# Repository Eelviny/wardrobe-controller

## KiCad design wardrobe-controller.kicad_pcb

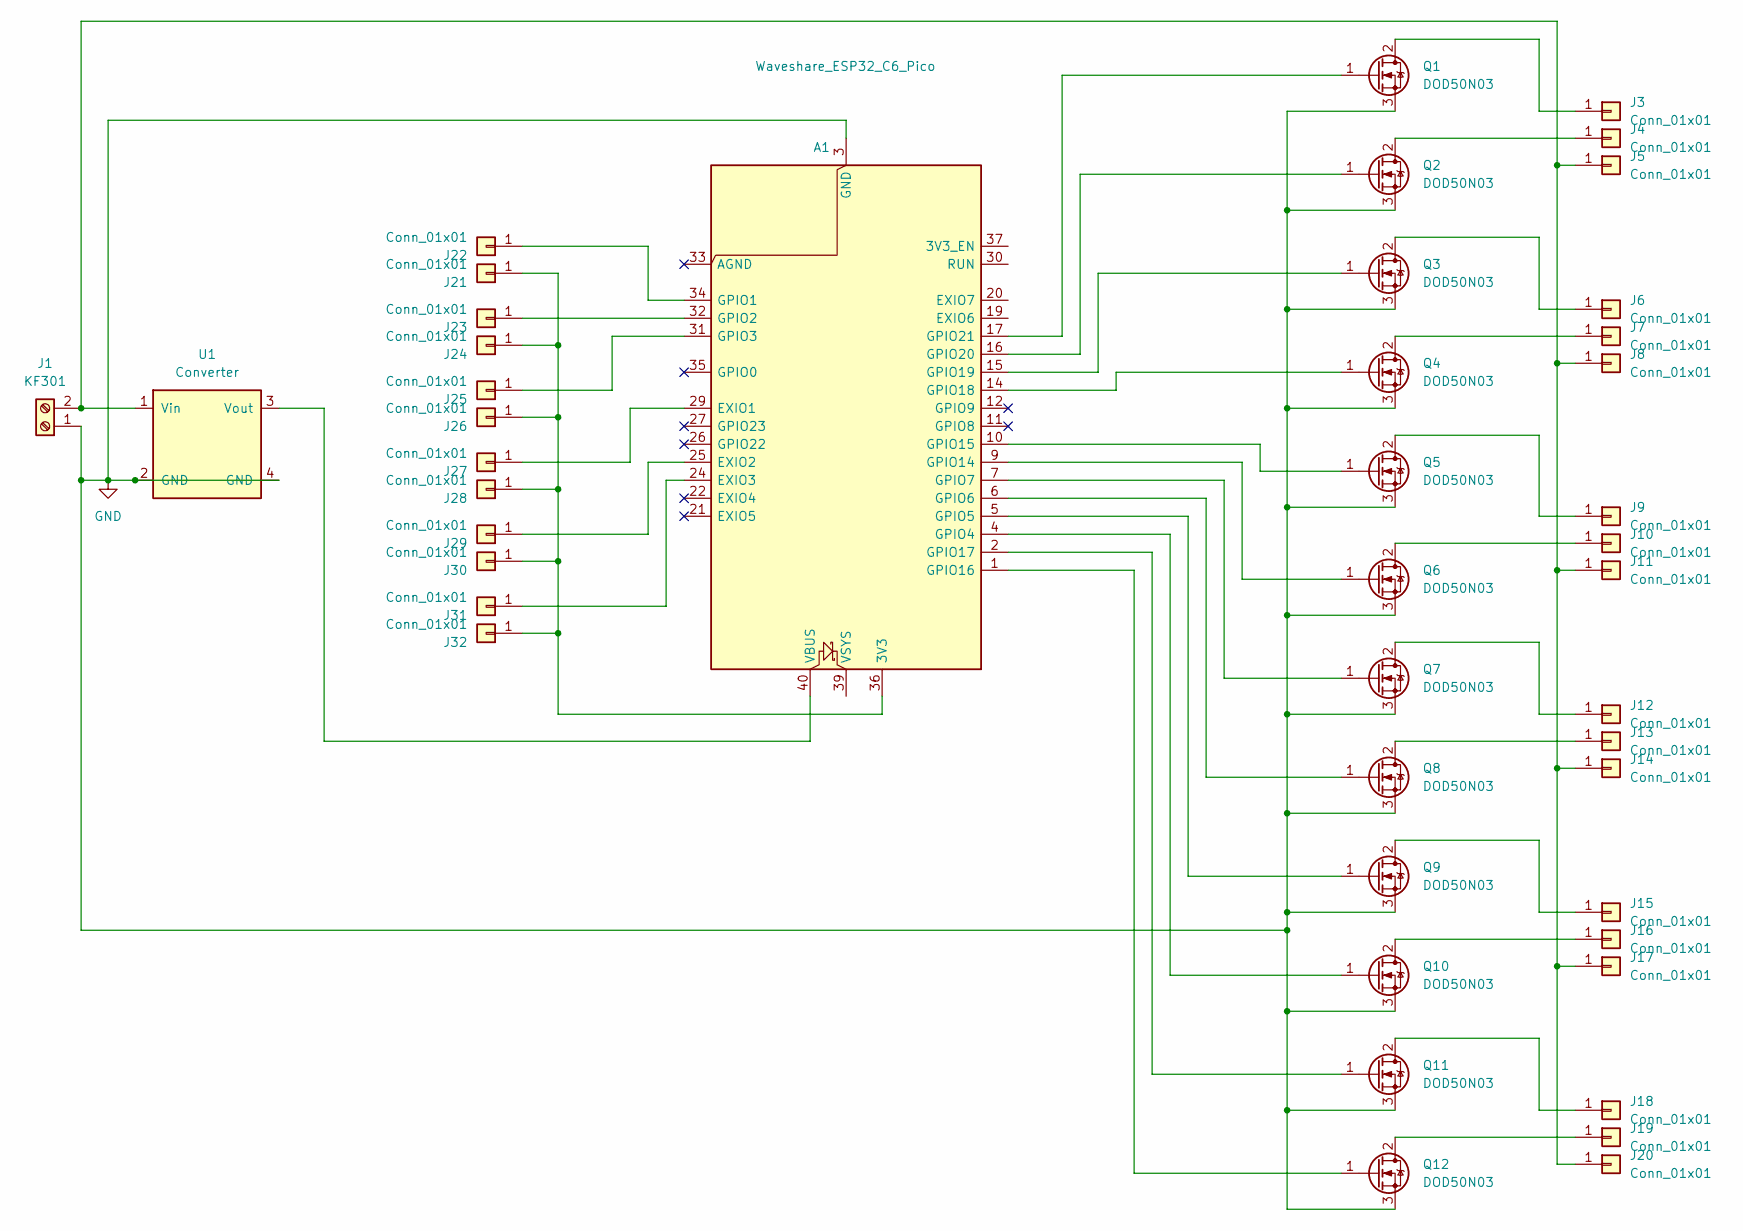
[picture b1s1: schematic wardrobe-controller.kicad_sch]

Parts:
A1: Waveshare_ESP32_C6_Pico; RaspberryPi_Pico_Common
J1: KF301; TerminalBlock_RND_205-00012_1x02_P5.00mm_Horizontal; JLCPCB_IGNORE yes
J3, J4, J5, J6, J7, J8, J9, J10, J11, J12, J13, J14, J15, J16, J17, J18, J19, J20, J21, J22, J23, J24, J25, J26, J27, J28, J29, J30, J31, J32: Conn_01x01; SolderPad; JLCPCB_IGNORE yes
Q1, Q2, Q3, Q4, Q5, Q6, Q7, Q8, Q9, Q10, Q11, Q12: DOD50N03; TO-252-2; LCSC C36499176
U1: Converter; Buck_Converter_Module

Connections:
GND: A1.3 (GND), A1.8 (GND), A1.13 (GND), A1.18 (GND), A1.23 (GND), A1.28 (GND), A1.38 (GND), J1.1, Q1.3 (S), Q2.3 (S), Q3.3 (S), Q4.3 (S), Q5.3 (S), Q6.3 (S), Q7.3 (S), Q8.3 (S), Q9.3 (S), Q10.3 (S), Q11.3 (S), Q12.3 (S), U1.2 (GND), U1.4 (GND)
unnamed: A1.36 (3V3), J21.1, J24.1, J26.1, J28.1, J30.1, J32.1
unnamed: A1.29 (EXIO1), J27.1
unnamed: A1.25 (EXIO2), J29.1
unnamed: A1.24 (EXIO3), J31.1
unnamed: A1.34 (GPIO1), J22.1
unnamed: A1.32 (GPIO2), J23.1
unnamed: A1.31 (GPIO3), J25.1
unnamed: A1.4 (GPIO4), Q10.1 (G)
unnamed: A1.5 (GPIO5), Q9.1 (G)
unnamed: A1.6 (GPIO6), Q8.1 (G)
unnamed: A1.7 (GPIO7), Q7.1 (G)
unnamed: A1.9 (GPIO14), Q6.1 (G)
unnamed: A1.10 (GPIO15), Q5.1 (G)
unnamed: A1.1 (GPIO16), Q12.1 (G)
unnamed: A1.2 (GPIO17), Q11.1 (G)
unnamed: A1.14 (GPIO18), Q4.1 (G)
unnamed: A1.15 (GPIO19), Q3.1 (G)
unnamed: A1.16 (GPIO20), Q2.1 (G)
unnamed: A1.17 (GPIO21), Q1.1 (G)
unnamed: A1.40 (VBUS), U1.3 (Vout)
unnamed: J1.2, J5.1, J8.1, J11.1, J14.1, J17.1, J20.1, U1.1 (Vin)
unnamed: J3.1, Q1.2 (D)
unnamed: J4.1, Q2.2 (D)
unnamed: J6.1, Q3.2 (D)
unnamed: J7.1, Q4.2 (D)
unnamed: J9.1, Q5.2 (D)
unnamed: J10.1, Q6.2 (D)
unnamed: J12.1, Q7.2 (D)
unnamed: J13.1, Q8.2 (D)
unnamed: J15.1, Q9.2 (D)
unnamed: J16.1, Q10.2 (D)
unnamed: J18.1, Q11.2 (D)
unnamed: J19.1, Q12.2 (D)

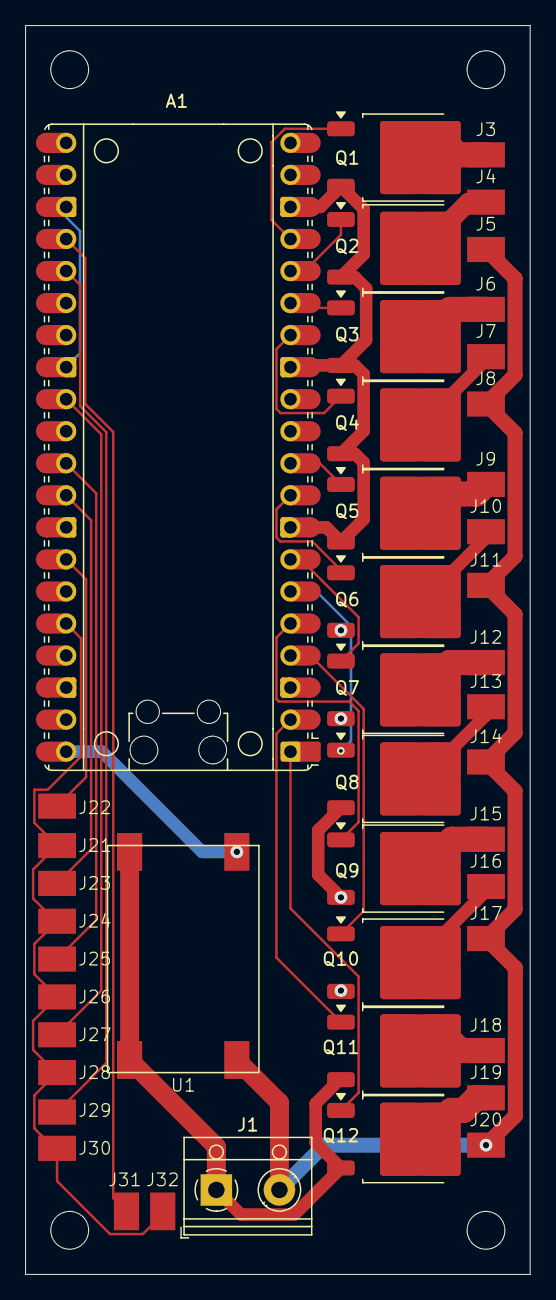
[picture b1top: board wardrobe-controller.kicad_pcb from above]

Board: 2 copper layers, 40.0 x 99.0 mm, 45 parts (0 on the bottom side), 34 nets.

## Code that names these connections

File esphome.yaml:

esphome:
  name: wardrobe
  friendly_name: Wardrobe
  platformio_options:
    board_build.flash_mode: dio
    build_flags: "-DI2C_NUM_1=I2C_NUM_0"
  on_boot:
    then:
      - light.control:
          id: light_1
          state: off
          brightness: 80%
      - light.control:
          id: light_2
          state: off
          brightness: 80%
      - light.control:
          id: light_3
          state: off
          brightness: 80%
      - light.control:
          id: light_4
          state: off
          brightness: 80%

esp32:
  board: esp32-c6-devkitc-1
  variant: ESP32C6
  flash_size: 4MB
  framework:
    type: esp-idf
i2c:
  scan: false
  sda: GPIO22
  scl: GPIO23
  frequency: 400kHz

pca9554:
  - id: "pca9554a_device"

# Enable logging
# logger:
#   hardware_uart: USB_SERIAL_JTAG

api:
  reboot_timeout: 8h
  encryption:
    key: !secret encryption_key

ota:
  - platform: esphome

wifi:
  ssid: !secret wifi_ssid
  password: !secret wifi_password

# esp32_improv:
#   authorizer: none
#   identify_duration: 30s

network:
  enable_ipv6: true

sensor:
  - platform: uptime
    name: Uptime
    id: uptime_sensor
  - platform: wifi_signal
    name: Signal Strength
    id: wifi_sensor

button:
  - platform: restart
    name: Restart
  - platform: safe_mode
    name: Restart (Safe Mode)

switch:
  - platform: template
    id: door_activation
    name: Door Open Activation
    optimistic: true
    icon: mdi:lightbulb-auto
    restore_mode: RESTORE_DEFAULT_ON

output:
  - platform: ledc
    id: warm_white_output_3
    frequency: 9765Hz
    pin:
      number: GPIO15
  # - platform: ledc
  #   id: cold_white_output_3
  #   frequency: 9765Hz
  #   pin:
  #     number: GPIO14
  - platform: gpio
    id: cold_white_output_3
    pin:
      number: GPIO14
  - platform: ledc
    id: warm_white_output_4
    frequency: 9765Hz
    phase_angle: 90
    pin:
      number: GPIO7
  - platform: gpio
    id: cold_white_output_4
    pin:
      number: GPIO6
  # - platform: ledc
  #   id: cold_white_output_4
  #   frequency: 9765Hz
  #   pin:
  #     number: GPIO6
  - platform: ledc
    id: warm_white_output_5
    frequency: 9765Hz
    phase_angle: 180
    pin:
      number: GPIO5
  - platform: gpio
    id: cold_white_output_5
    pin:
      number: GPIO4
  # - platform: ledc
  #   id: cold_white_output_5
  #   frequency: 9765Hz
  #   pin:
  #     number: GPIO4
  - platform: ledc
    id: warm_white_output_6
    frequency: 9765Hz
    phase_angle: 270
    pin:
      number: GPIO17
  - platform: gpio
    id: cold_white_output_6
    pin:
      number: GPIO16
  # - platform: ledc
  #   id: cold_white_output_6
  #   frequency: 9765Hz
  #   pin:
  #     number: GPIO16

light:
  # - platform: esp32_rmt_led_strip
  #   rgb_order: RGB
  #   pin: GPIO8
  #   num_leds: 1
  #   chipset: ws2812
  #   name: "Status LED"
  #   default_transition_length: 0s
  #   disabled_by_default: true
  # - platform: cwww
  #   id: light_1
  #   name: Light 1
  #   warm_white: warm_white_output_3
  #   cold_white: cold_white_output_3
  #   cold_white_color_temperature: 6500 K
  #   warm_white_color_temperature: 2700 K
  # - platform: cwww
  #   id: light_2
  #   name: Light 2
  #   warm_white: warm_white_output_4
  #   cold_white: cold_white_output_4
  #   cold_white_color_temperature: 6500 K
  #   warm_white_color_temperature: 2700 K
  # - platform: cwww
  #   id: light_3
  #   name: Light 3
  #   warm_white: warm_white_output_5
  #   cold_white: cold_white_output_5
  #   cold_white_color_temperature: 6500 K
  #   warm_white_color_temperature: 2700 K
  # - platform: cwww
  #   id: light_4
  #   name: Light 4
  #   warm_white: warm_white_output_6
  #   cold_white: cold_white_output_6
  #   cold_white_color_temperature: 6500 K
  #   warm_white_color_temperature: 2700 K
  - platform: monochromatic
    name: Light 1
    id: light_1
    output: warm_white_output_3
    restore_mode: ALWAYS_OFF
  - platform: monochromatic
    name: Light 2
    id: light_2
    output: warm_white_output_4
    restore_mode: ALWAYS_OFF
  - platform: monochromatic
    name: Light 3
    id: light_3
    output: warm_white_output_5
    restore_mode: ALWAYS_OFF
  - platform: monochromatic
    name: Light 4
    id: light_4
    output: warm_white_output_6
    restore_mode: ALWAYS_OFF
  - platform: binary
    id: light_1_cold
    output: cold_white_output_3
    restore_mode: ALWAYS_OFF
  - platform: binary
    id: light_2_cold
    output: cold_white_output_4
    restore_mode: ALWAYS_OFF
  - platform: binary
    id: light_3_cold
    output: cold_white_output_5
    restore_mode: ALWAYS_OFF
  - platform: binary
    id: light_4_cold
    output: cold_white_output_6
    restore_mode: ALWAYS_OFF

binary_sensor:
  - platform: gpio
    pin:
      number: GPIO1
      mode:
        input: true
        pulldown: true
    id: door_1
    filters:
      - delayed_on_off: 20ms
    on_press:
      - if:
          condition:
            switch.is_on: door_activation
          then:
            - light.turn_off:
                id: light_1
    on_release:
      - if:
          condition:
            switch.is_on: door_activation
          then:
            - light.turn_on:
                id: light_1
  - platform: gpio
    pin:
      number: GPIO2
      mode:
        input: true
        pulldown: true
    id: door_2
    filters:
      - delayed_on_off: 20ms
    on_press:
      - if:
          condition:
            switch.is_on: door_activation
          then:
            - light.turn_off:
                id: light_2
    on_release:
      - if:
          condition:
            switch.is_on: door_activation
          then:
            - light.turn_on:
                id: light_2
  - platform: gpio
    pin:
      number: GPIO3
      mode:
        input: true
        pulldown: true
    id: door_3
    filters:
      - delayed_on_off: 20ms
    on_press:
      - if:
          condition:
            switch.is_on: door_activation
          then:
            - light.turn_off:
                id: light_3
    on_release:
      - if:
          condition:
            switch.is_on: door_activation
          then:
            - light.turn_on:
                id: light_3
  - platform: gpio
    pin:
      pca9554: pca9554a_device
      number: 0
      mode:
        input: true
      inverted: true
    id: door_4
    filters:
      - delayed_on_off: 20ms
    on_press:
      - if:
          condition:
            switch.is_on: door_activation
          then:
            - light.turn_off:
                id: light_4
    on_release:
      - if:
          condition:
            switch.is_on: door_activation
          then:
            - light.turn_on:
                id: light_4

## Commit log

2026-01-08 feat: init
2026-01-08 Add MIT License to the project
2026-01-08 feat: add esphome config
